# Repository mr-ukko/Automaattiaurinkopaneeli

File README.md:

https://github.com/user-attachments/assets/cd2b4438-9945-49b4-82a4-f631b56c392a

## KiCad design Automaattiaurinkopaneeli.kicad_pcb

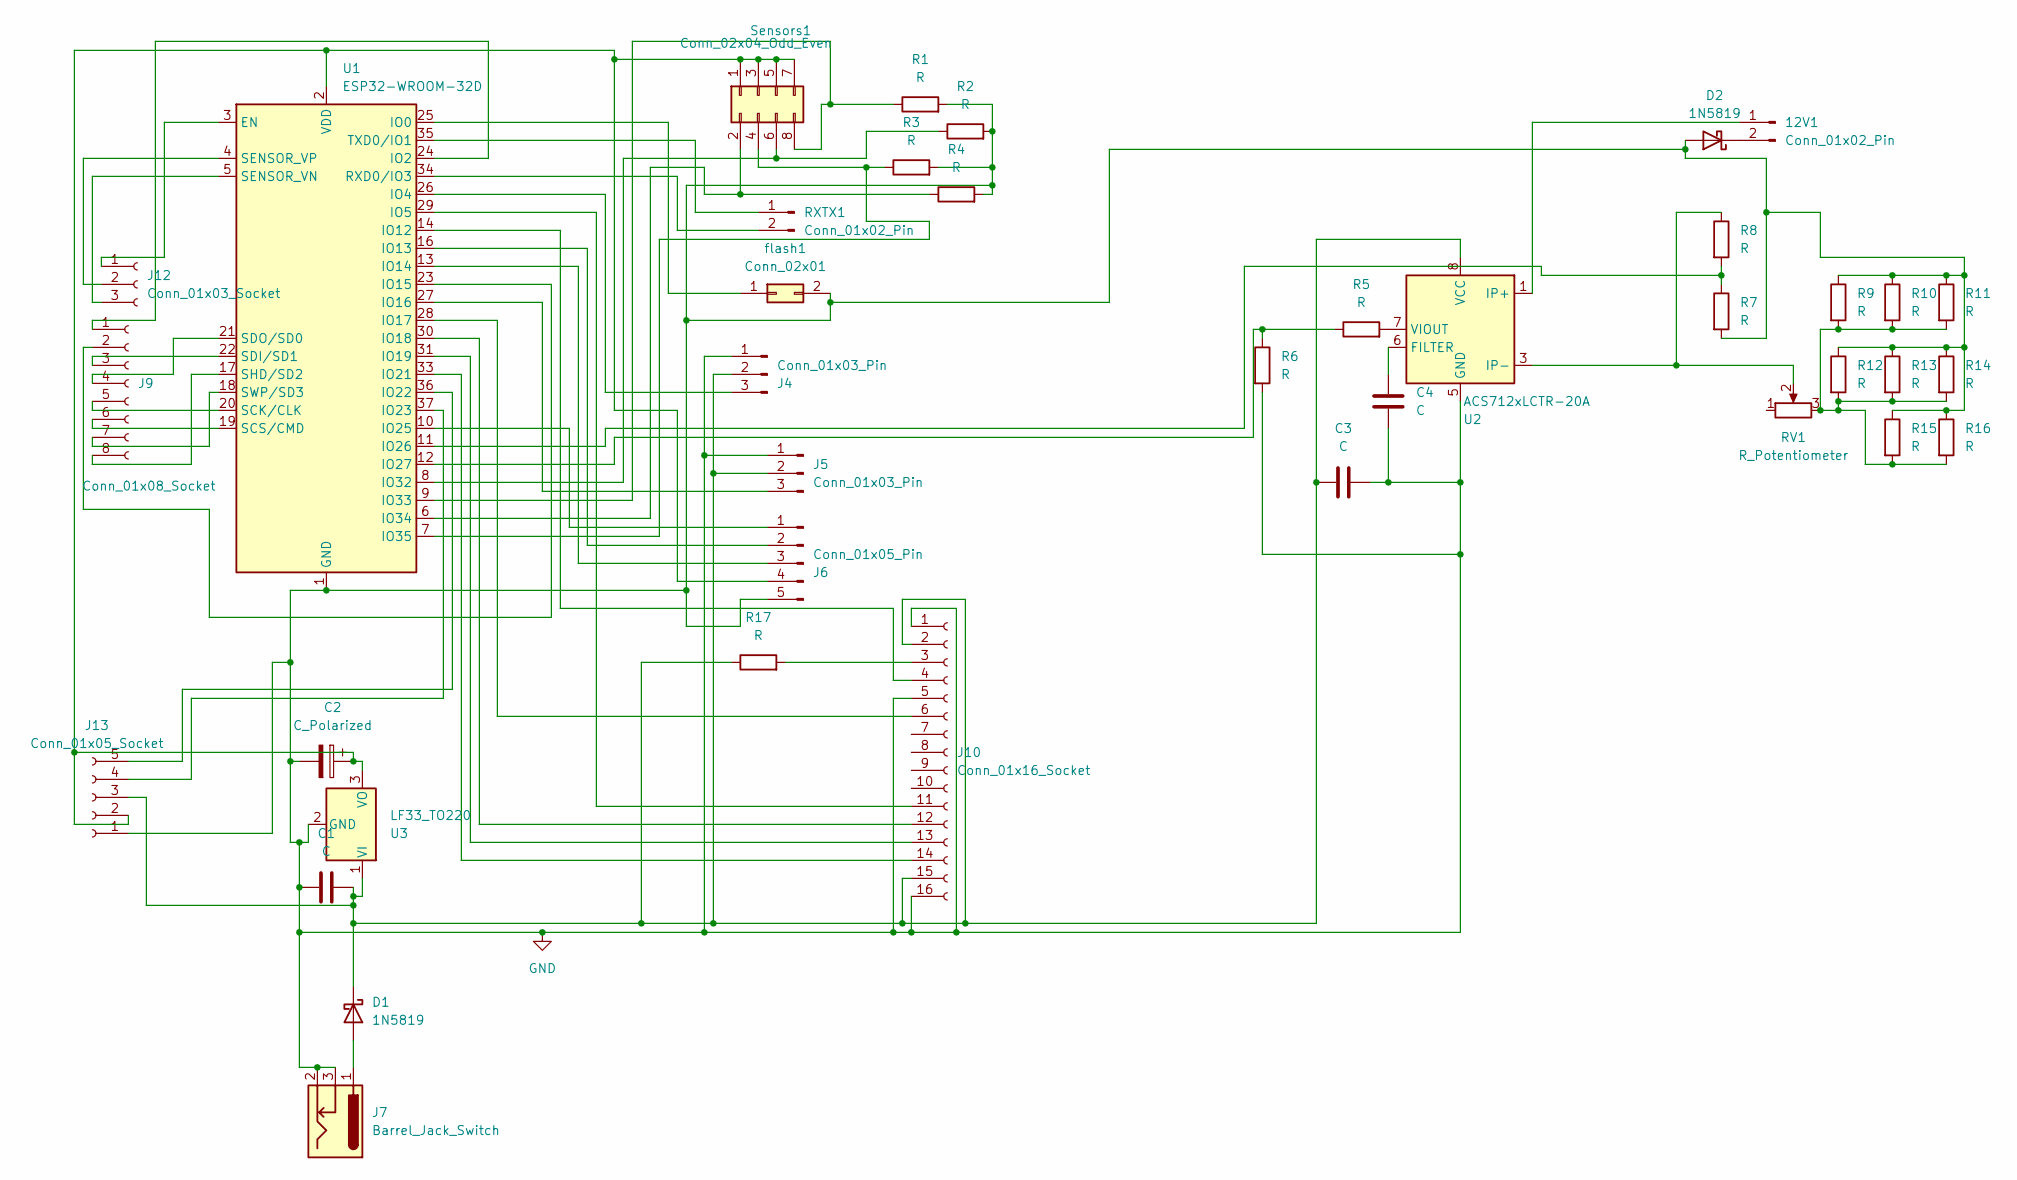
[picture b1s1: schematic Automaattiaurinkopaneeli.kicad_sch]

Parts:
12V1: Conn_01x02_Pin; PinHeader_1x02_P2.54mm_Vertical
C1: C; C_Rect_L7.0mm_W3.5mm_P5.00mm
C2: C_Polarized; CP_Radial_D5.0mm_P2.00mm
C3, C4: C; C_Disc_D10.0mm_W2.5mm_P5.00mm
D1, D2: 1N5819; D_DO-41_SOD81_P10.16mm_Horizontal
J4, J5: Conn_01x03_Pin; PinHeader_1x03_P2.54mm_Vertical
J6: Conn_01x05_Pin; PinHeader_1x05_P2.54mm_Vertical
J7: Barrel_Jack_Switch; BarrelJack_Wuerth_6941xx301002
J9: Conn_01x08_Socket; PinSocket_1x08_P2.54mm_Vertical
J10: Conn_01x16_Socket; PinSocket_1x16_P2.54mm_Vertical
J12: Conn_01x03_Socket; PinSocket_1x03_P2.54mm_Vertical
J13: Conn_01x05_Socket; PinHeader_1x05_P2.54mm_Vertical
R1, R2, R3, R4, R5, R6, R7, R8, R9, R10, R11, R12, R13, R14, R15, R16, R17: R; R_Axial_DIN0207_L6.3mm_D2.5mm_P10.16mm_Horizontal
RV1: R_Potentiometer; Potentiometer_Generic_148-149_Single_Horizontal
RXTX1: Conn_01x02_Pin; PinHeader_1x02_P2.54mm_Vertical
Sensors1: Conn_02x04_Odd_Even; PinSocket_2x04_P2.54mm_Vertical
U1: ESP32-WROOM-32D
U2: ACS712xLCTR-20A; SOIC-8_3.9x4.9mm_P1.27mm
U3: LF33_TO220; TO-220-3_Vertical
flash1: Conn_02x01; PinHeader_2x01_P2.54mm_Vertical

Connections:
GND: C1.1, C2.2, C3.2, C4.2, D2.2 (A), J4.1, J5.1, J6.5, J7.2, J7.3, J10.1, J10.5, J10.16, J13.1, R1.2, R2.2, R3.2, R4.2, R6.2, R7.2, R9.1, R10.1, R11.1, R12.1, R13.1, R14.1, R15.1, R16.1, U1.1 (GND), U1.15 (GND), U1.38 (GND), U1.39 (GND), U2.5 (GND), U3.2 (GND), flash1.2
unnamed: 12V1.1, U2.1 (IP+), U2.2 (IP+)
unnamed: 12V1.2, D2.1 (K)
unnamed: D1.2 (A), J7.1
unnamed: C1.2, C3.1, D1.1 (K), J4.2, J5.2, J10.2, J10.15, J13.3, R17.1, U2.8 (VCC), U3.1 (VI)
unnamed: J4.3, U1.26 (IO4)
unnamed: J5.3, U1.27 (IO16)
unnamed: J6.1, U1.10 (IO25)
unnamed: J6.2, U1.16 (IO13)
unnamed: J6.3, U1.13 (IO14)
unnamed: J9.1, U1.24 (IO2)
unnamed: J9.2, U1.23 (IO15)
unnamed: J9.3, U1.22 (SDI/SD1)
unnamed: J9.4, U1.21 (SDO/SD0)
unnamed: J9.5, U1.20 (SCK/CLK)
unnamed: J9.6, U1.19 (SCS/CMD)
unnamed: J9.7, U1.18 (SWP/SD3)
unnamed: J9.8, U1.17 (SHD/SD2)
unnamed: J10.3, R17.2
unnamed: J10.4, U1.14 (IO12)
unnamed: J10.6, U1.28 (IO17)
unnamed: J10.11, U1.29 (IO5)
unnamed: J10.12, U1.30 (IO18)
unnamed: J10.13, U1.31 (IO19)
unnamed: J10.14, U1.33 (IO21)
unnamed: J12.1, U1.3 (EN)
unnamed: J12.2, U1.4 (SENSOR_VP)
unnamed: J12.3, U1.5 (SENSOR_VN)
unnamed: C2.1, J6.4, J13.2, Sensors1.1, Sensors1.3, Sensors1.5, Sensors1.7, U1.2 (VDD), U3.3 (VO)
unnamed: J13.4, U1.37 (IO23)
unnamed: J13.5, U1.36 (IO22)
unnamed: R8.1, RV1.2, U2.3 (IP-), U2.4 (IP-)
unnamed: R9.2, R10.2, R11.2, R12.2, R13.2, R14.2, R15.2, R16.2, RV1.3
unnamed: RXTX1.1, U1.35 (TXD0/IO1)
unnamed: RXTX1.2, U1.34 (RXD0/IO3)
unnamed: R4.1, Sensors1.2, U1.6 (IO34)
unnamed: R3.1, Sensors1.4, U1.7 (IO35)
unnamed: R2.1, Sensors1.6, U1.8 (IO32)
unnamed: R1.1, Sensors1.8, U1.9 (IO33)
unnamed: U1.25 (IO0), flash1.1
unnamed: R7.1, R8.2, U1.11 (IO26)
unnamed: R5.1, R6.1, U1.12 (IO27)
unnamed: C4.1, U2.6 (FILTER)
unnamed: R5.2, U2.7 (VIOUT)

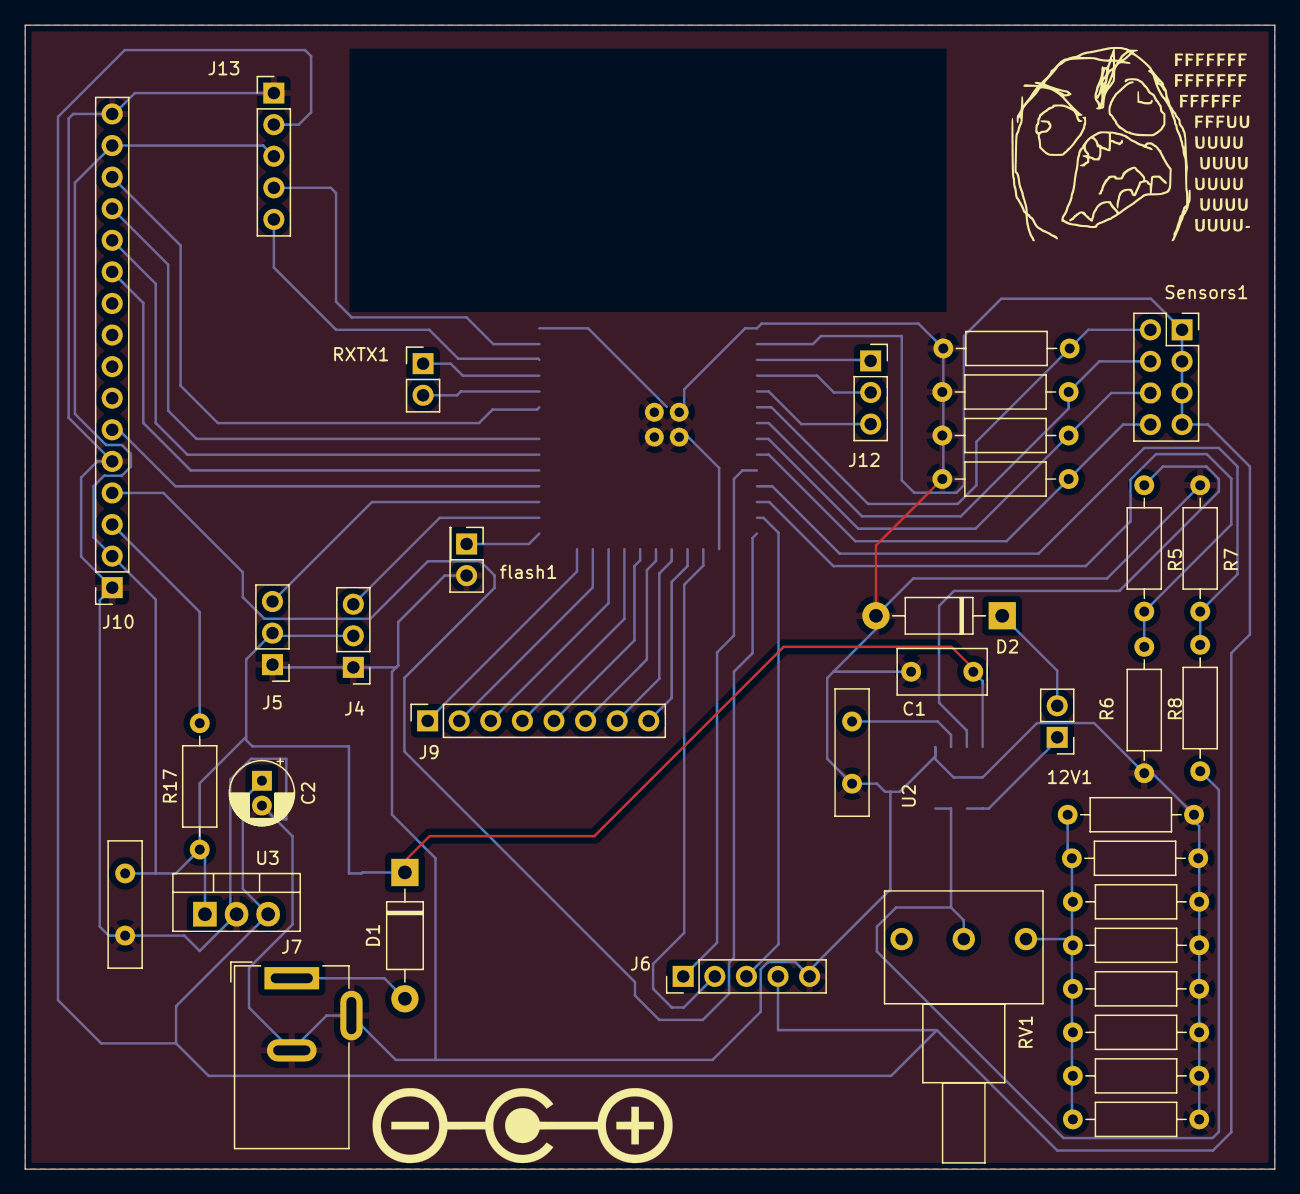
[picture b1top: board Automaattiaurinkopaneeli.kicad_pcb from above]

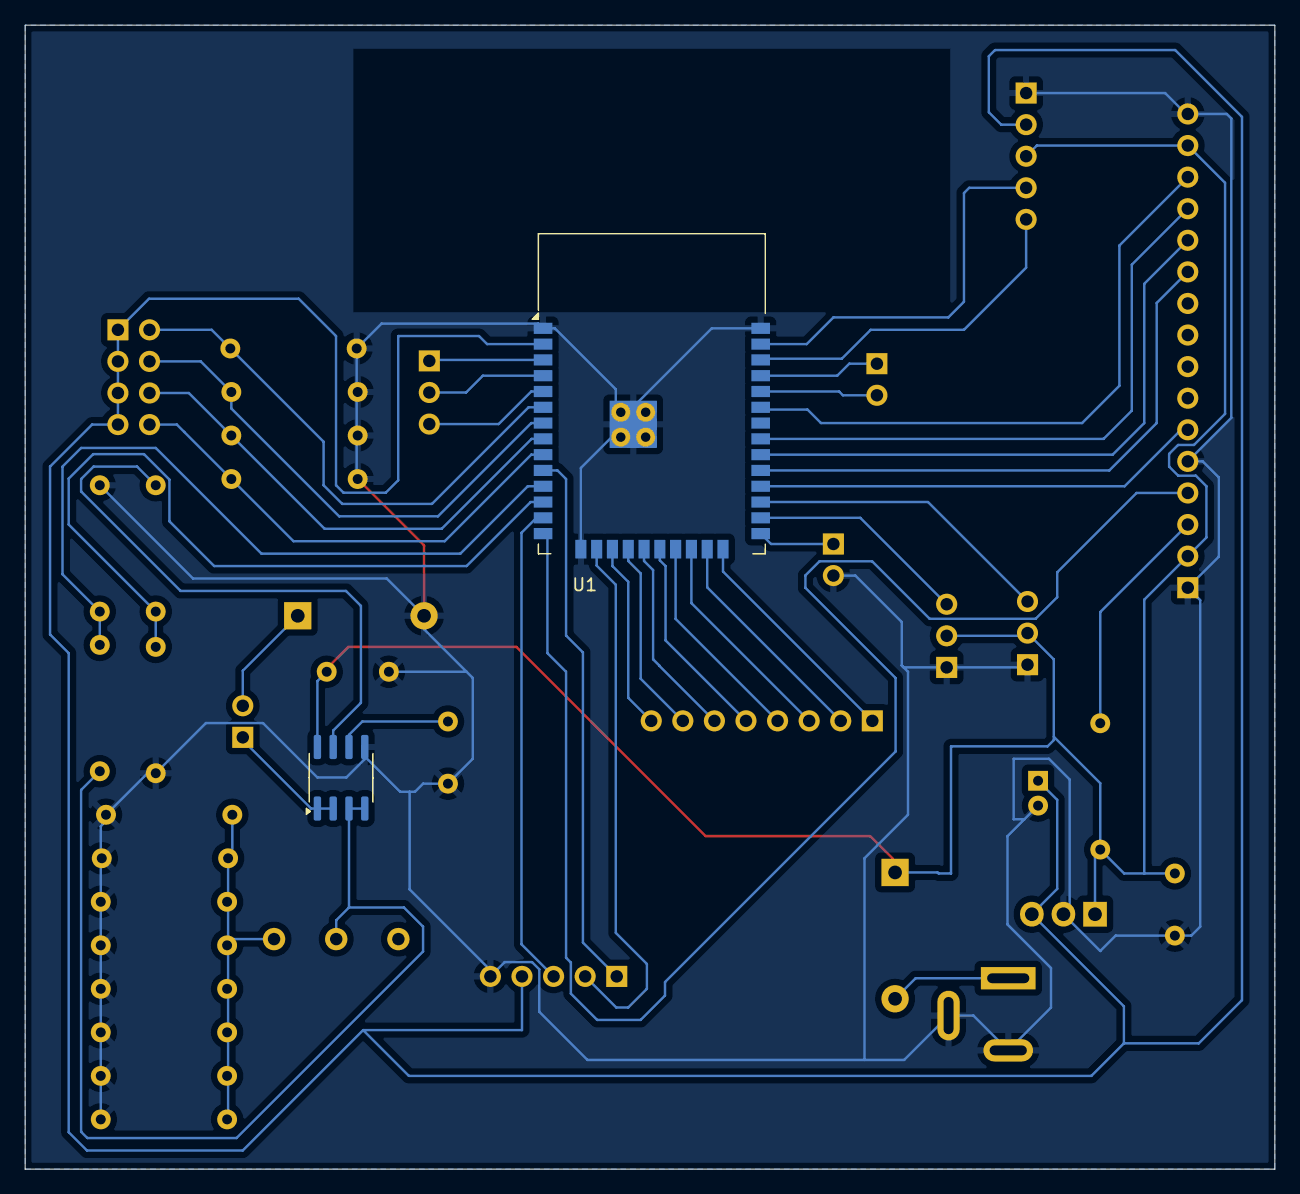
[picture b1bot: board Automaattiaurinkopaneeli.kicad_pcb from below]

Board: 2 copper layers, 100.5 x 92.0 mm, 39 parts (2 on the bottom side), 44 nets.

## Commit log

2024-03-23 initial
2024-03-27 still not finished
2024-03-28 end of day and final desing
2024-04-01 v0.6
2024-04-02 code
2024-04-09 voltage meter
2024-04-23 final code
